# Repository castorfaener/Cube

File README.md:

# Cube
Proyecto de cubo multisensorial

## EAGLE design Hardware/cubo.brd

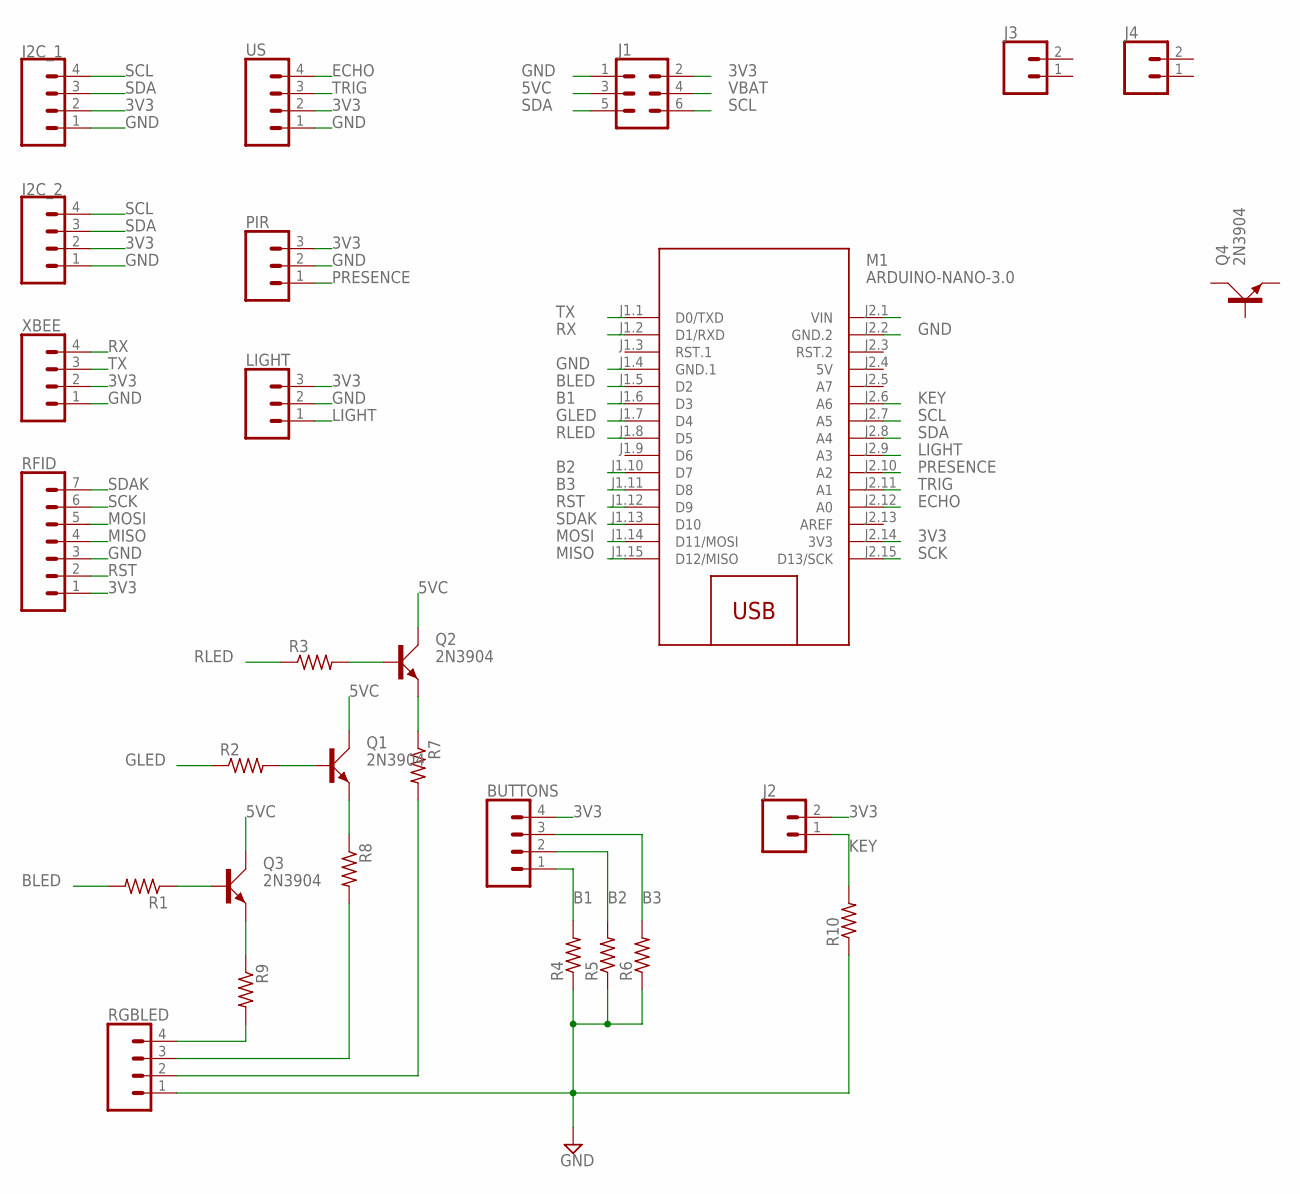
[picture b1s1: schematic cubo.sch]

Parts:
BUTTONS: CONN_04JST-PTH-VERT; JST-4-PTH-VERT
I2C_1, I2C_2: CONN_04JST-PTH-VERT; JST-4-PTH-VERT
J1: CONN_03X2SHROUD; 2X3-SHROUDED
J2, J3, J4: CONN_02POLAR_LOCK; MOLEX-1X2_LOCK
LIGHT: CONN_03JST-PTH-VERT; JST-3-PTH-VERT
M1: ARDUINO-NANO-3.0
PIR: CONN_03JST-PTH-VERT; JST-3-PTH-VERT
Q1, Q2, Q3, Q4: 2N3904; TO92D
R1, R2, R3, R4, R5, R6, R7, R8, R9, R10: R-US_0207/10; 0207/10
RFID: CONN_07; 1X07
RGBLED: CONN_04JST-PTH-VERT; JST-4-PTH-VERT
US: CONN_04JST-PTH-VERT; JST-4-PTH-VERT
XBEE: CONN_04JST-PTH-VERT; JST-4-PTH-VERT

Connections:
3V3: BUTTONS.4, I2C_1.2, I2C_2.2, J1.2, J2.2, LIGHT.3, M1.J2.14 (3V3), PIR.3, RFID.1, US.2, XBEE.2
5V: M1.J2.4 (5V)
5VC: J1.3, Q1.C, Q2.C, Q3.C
B1: BUTTONS.1, M1.J1.6 (D3), R4.2
B2: BUTTONS.2, M1.J1.10 (D7), R5.2
B3: BUTTONS.3, M1.J1.11 (D8), R6.2
BLED: M1.J1.5 (D2), R1.2
ECHO: M1.J2.12 (A0), US.4
GLED: M1.J1.7 (D4), R2.1
GND: I2C_1.1, I2C_2.1, J1.1, LIGHT.2, M1.J1.4 (GND.1), M1.J2.2 (GND.2), PIR.2, R4.1, R5.1, R6.1, R10.1, RFID.3, RGBLED.1, US.1, XBEE.1
KEY: J2.1, M1.J2.6 (A6), R10.2
LIGHT: LIGHT.1, M1.J2.9 (A3)
MISO: M1.J1.15 (D12/MISO), RFID.4
MOSI: M1.J1.14 (D11/MOSI), RFID.5
unnamed: Q2.B, R3.2
unnamed: Q1.B, R2.2
unnamed: Q3.B, R1.1
unnamed: Q3.E, R9.1
unnamed: Q1.E, R8.1
unnamed: Q2.E, R7.1
unnamed: R9.2, RGBLED.4
unnamed: R8.2, RGBLED.3
unnamed: R7.2, RGBLED.2
PRESENCE: M1.J2.10 (A2), PIR.1
RLED: M1.J1.8 (D5), R3.1
RST: M1.J1.12 (D9), RFID.2
RX: M1.J1.2 (D1/RXD), XBEE.4
SCK: M1.J2.15 (D13/SCK), RFID.6
SCL: I2C_1.4, I2C_2.4, J1.6, M1.J2.7 (A5)
SDA: I2C_1.3, I2C_2.3, J1.5, M1.J2.8 (A4)
SDAK: M1.J1.13 (D10), RFID.7
TRIG: M1.J2.11 (A1), US.3
TX: M1.J1.1 (D0/TXD), XBEE.3
VBAT: J1.4

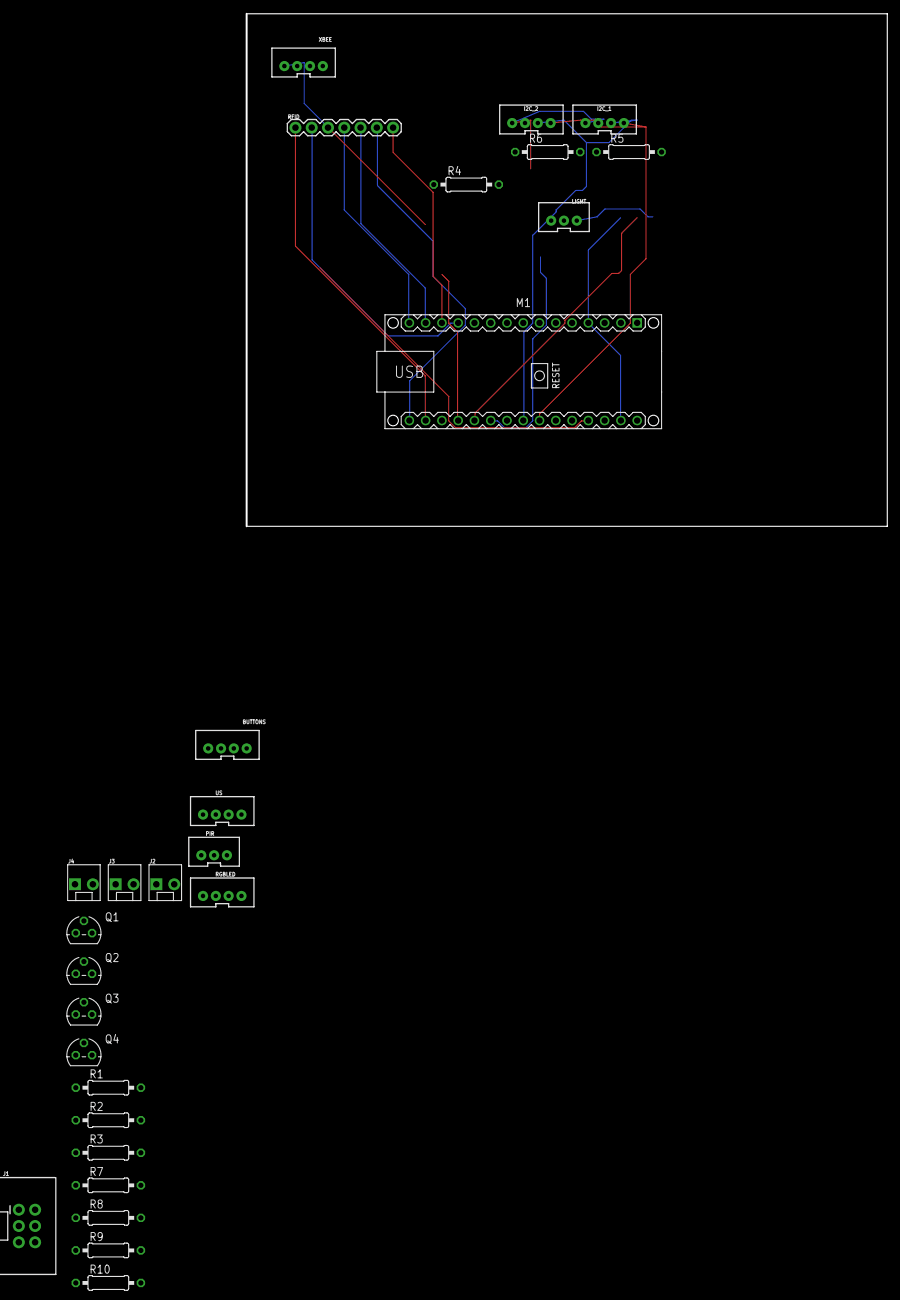
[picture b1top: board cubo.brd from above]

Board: 2 copper layers, 100.0 x 80.0 mm, 28 parts (0 on the bottom side), 32 nets.

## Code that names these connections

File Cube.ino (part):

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bool button1_state;                   //Control del estado de los botones
bool button2_state; 

#define RLed_Pin 5              //Definimos los pines del Led RGB
#define GLed_Pin 3
#define BLed_Pin 2

#define Buzz_Pin 6               //Definimos el pin del zumbador

#define Trig_Pin A1              //Definimos los pines del sensor de US
#define Echo_Pin A0

#define Pres_Pin A3              //Definimos el pin del sensor de presencia

#define Light_Pin A2             //Definimos el pin del sensor de luz

#define Key_Pin 8               //Definimos el pin del interruptor de llave

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    	while (1);
	}

  	pinMode(RLed_Pin, OUTPUT);            //Configuramos los pines de E/S
  	pinMode(GLed_Pin, OUTPUT);
  	pinMode(BLed_Pin, OUTPUT);
  	pinMode(Trig_Pin, OUTPUT);
  	pinMode(Echo_Pin, INPUT);
  	pinMode(Pres_Pin, INPUT);
  	pinMode(Light_Pin, INPUT);
  	pinMode(Key_Pin, INPUT);
  	pinMode(Button1_Pin, INPUT);
  	pinMode(Button2_Pin, INPUT);
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  Serial1.println(".");
  delay(500);

  cm = US(Trig_Pin, Echo_Pin);
  Serial1.print("Distancia al objeto: ");
  Serial1.print(cm);
  Serial1.println("cm");
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  Serial1.println("Realizamos 10 medidas en 5 segundos:");
  for(int i = 0 ; i < 10 ; i++ )
{
    Light = analogRead(Light_Pin);
    Light = map(Light, 0, 100, 0, 255);
    Serial1.print("Sensor de luz al ");
    Serial1.print(Light);
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  	switch(color)
	{	
    	case 0:
		digitalWrite(RLed_Pin, 0);                    //Apagamos el led
		digitalWrite(GLed_Pin, 0);
		digitalWrite(BLed_Pin, 0);
		break;
		case 1:  
		digitalWrite(RLed_Pin, 255);                    //Rojo
		digitalWrite(GLed_Pin, 0);
		digitalWrite(BLed_Pin, 0);
		break;
		case 2:  
		digitalWrite(RLed_Pin, 0);                    //Verde
		digitalWrite(GLed_Pin, 255);
		digitalWrite(BLed_Pin, 0);
		break;
		case 3:  
		digitalWrite(RLed_Pin, 0);                    //Azul
		digitalWrite(GLed_Pin, 0);
		digitalWrite(BLed_Pin, 255);
		break;  
		case 4:  
		digitalWrite(RLed_Pin, 255);                    //Blanco
		digitalWrite(GLed_Pin, 255);
		digitalWrite(BLed_Pin, 255);
		break; 
		case 5:  
		digitalWrite(RLed_Pin, 255);                    //Amarillo
		digitalWrite(GLed_Pin, 255);
		digitalWrite(BLed_Pin, 0);
		break;   
		case 6:  
		digitalWrite(RLed_Pin, 255);                    //Rosa
		digitalWrite(GLed_Pin, 0);
		digitalWrite(BLed_Pin, 255);
		break;        
  	}
}
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
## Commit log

2019-11-05 Carga inicial del codigo
2019-11-14 Menu funcional
2019-11-21 Password_Movimientos Setup
2019-11-27 Moving psw funcional
2019-11-27 funcion led y modificacion de beep
2019-11-28 Display incluido
2019-11-29 Display sin delays
2019-12-01 Intento logo Display
2019-12-03 eliminamos la carpeta .vscode
2019-12-03 indexamos
2019-12-03 + sensibilidad en mov_psw
2019-12-04 Probando palabra tesoro (no funciona)
2019-12-04 Empezamos con TNT_setup
2019-12-06 Guardado sensibilidad en eeprom
2019-12-07 TNT_Setup funcional
2019-12-07 Empezamos con TNT
2019-12-09 TNT aadido limite
2019-12-09 TNT empezando modo
2019-12-10 TNT limites incluidos
2019-12-10 Depurando modo 2
2019-12-11 Display intro funcional
2019-12-12 Aadido selector modo en display
2019-12-13 Anyado guardado en EEprom en funcion de cambio de modo
2019-12-13 Incluimos control de habilitacion de sonido en funcion beep
2019-12-13 Menu Show Config modificado
2019-12-29 iniciando RFID

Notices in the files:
parts and their libraries:
SparkFun-Connectors: Licensing: Creative Commons ShareAlike 4.0 International - https://creativecommons.org/licenses/by-sa/4.0
diy-modules: Released under the Creative Commons Attribution 4.0 International License: http://creativecommons.org/licenses/by/4.0
